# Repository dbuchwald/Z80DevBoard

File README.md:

# Z80DevBoard
Simple Z80 based prototyping and development board designed as extension to Arduino Mega 2560

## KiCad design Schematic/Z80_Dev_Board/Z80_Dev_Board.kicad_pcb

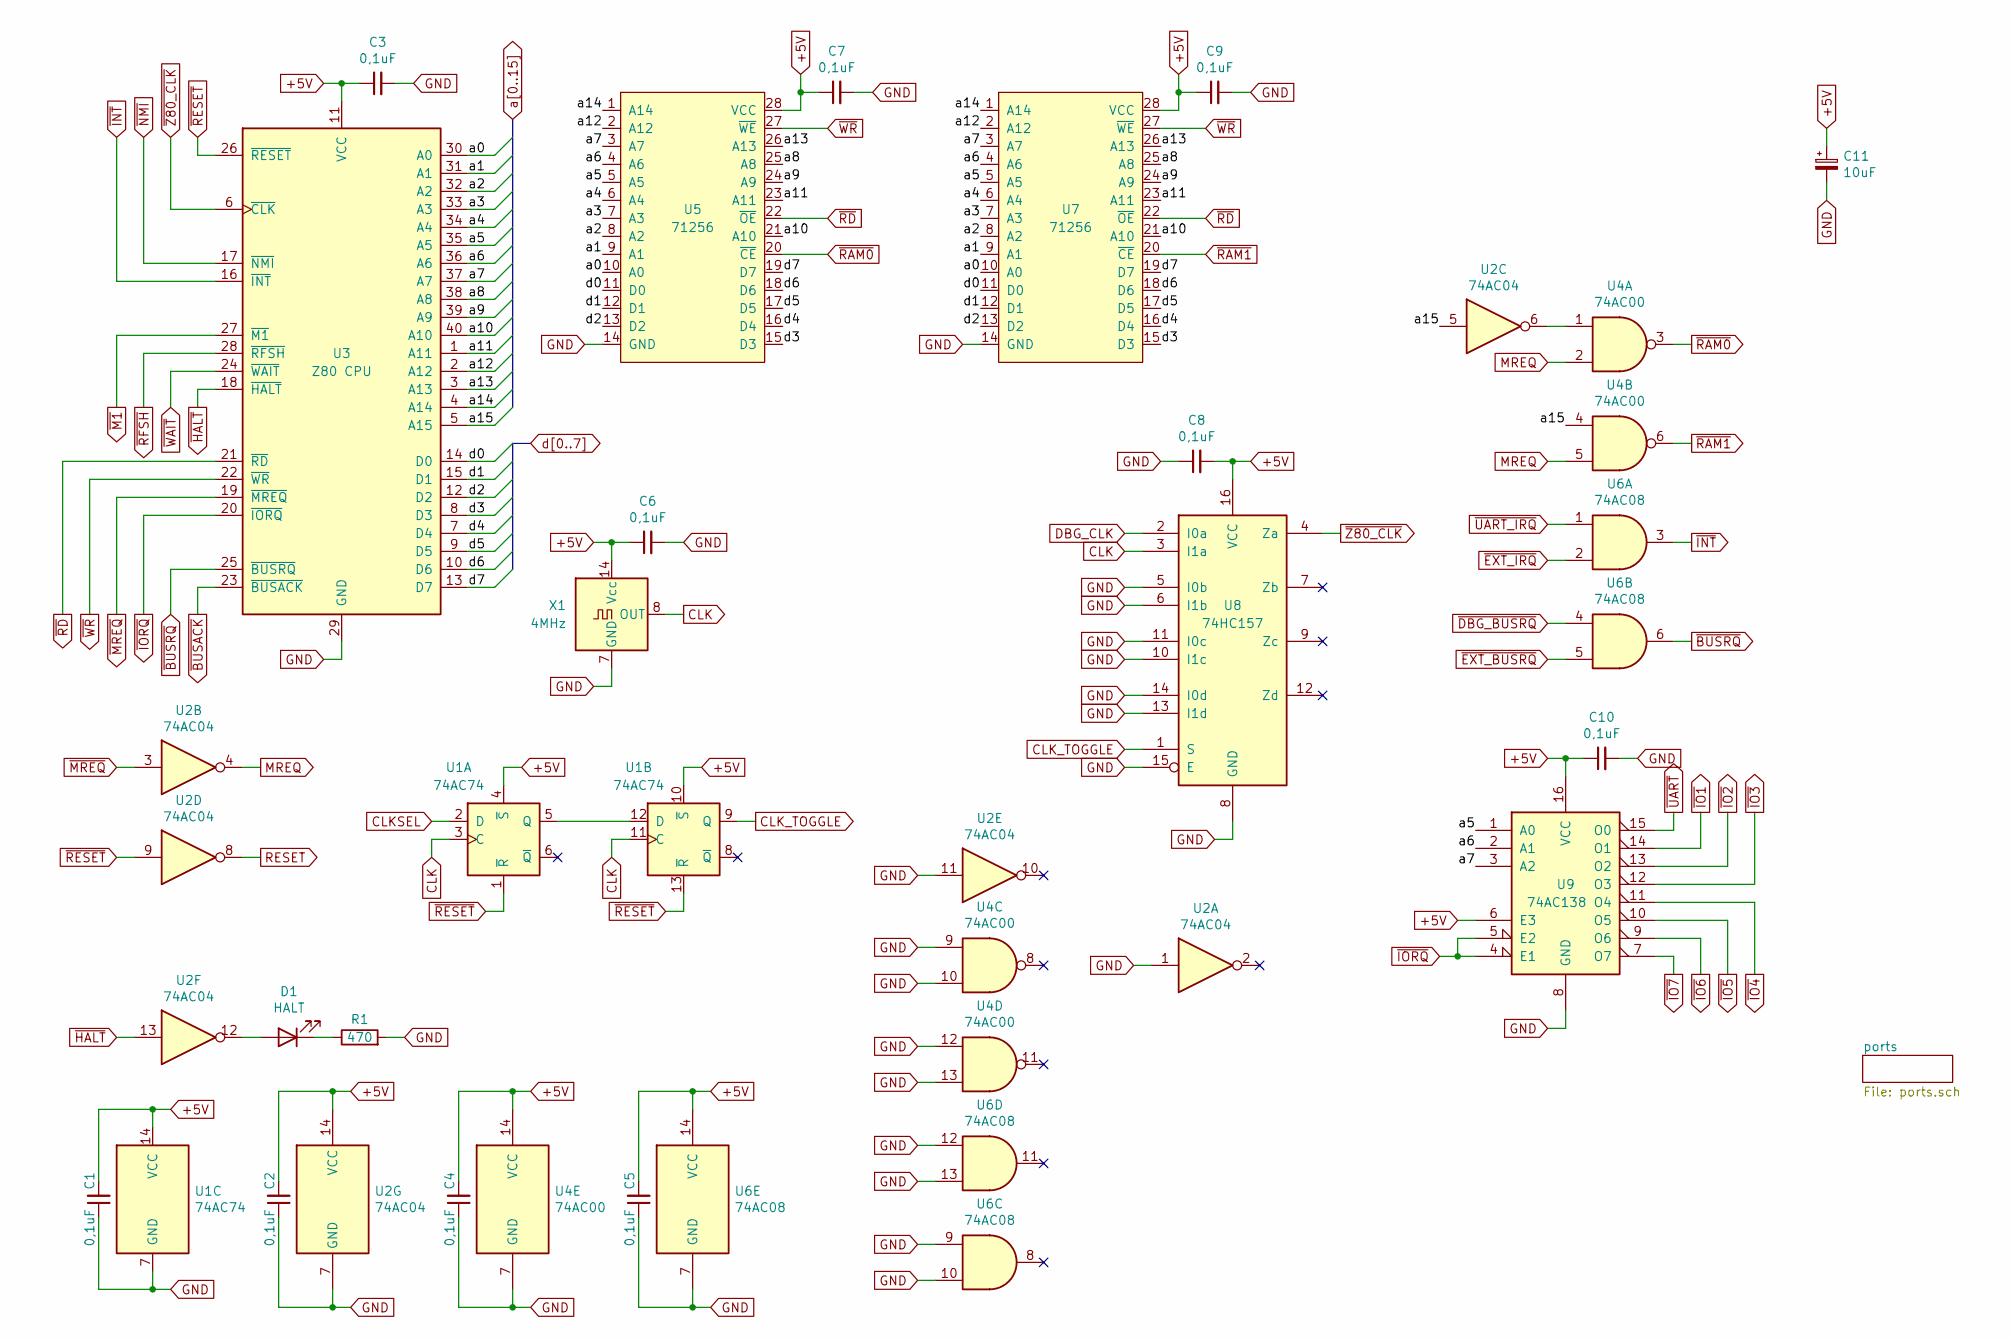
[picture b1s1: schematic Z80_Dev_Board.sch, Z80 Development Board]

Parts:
C1, C2, C3, C4, C5, C6, C7, C8, C9, C10: 0,1uF; C_1206_3216Metric_Pad1.42x1.75mm_HandSolder
C11: 10uF; CP_Radial_D4.0mm_P1.50mm
D1: HALT; LED_D3.0mm_Clear
R1: 470; R_1206_3216Metric_Pad1.30x1.75mm_HandSolder
U1: 74AC74; SOIC-14_3.9x8.7mm_P1.27mm
U2: 74AC04; SOIC-14_3.9x8.7mm_P1.27mm
U3: Z80 CPU; DIP-40_W15.24mm_Socket
U4: 74AC00; SOIC-14_3.9x8.7mm_P1.27mm
U5, U7: 71256; DIP-28_W7.62mm_Socket
U6: 74AC08; SOIC-14_3.9x8.7mm_P1.27mm
U8: 74HC157; SOIC-16_3.9x9.9mm_P1.27mm
U9: 74AC138; SOIC-16_3.9x9.9mm_P1.27mm
X1: 4MHz; Oscillator_DIP-14

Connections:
+5V: C1.2, C2.2, C3.1, C4.2, C5.2, C6.1, C7.1, C8.2, C9.1, C10.1, C11.1, U1.4 (~S), U1.10 (~S), U1.14 (VCC), U2.14 (VCC), U3.11 (VCC), U4.14 (VCC), U5.28 (VCC), U6.14 (VCC), U7.28 (VCC), U8.16 (VCC), U9.6 (E3), U9.16 (VCC), X1.14 (Vcc); also elsewhere on the board
CLK: U1.3 (C), U1.11 (C), U8.3 (I1a), X1.8 (OUT)
CLKSEL: U1.2 (D); also elsewhere on the board
CLK_TOGGLE: U1.9 (Q), U8.1 (S)
DBG_CLK: U8.2 (I0a); also elsewhere on the board
GND: C1.1, C2.1, C3.2, C4.1, C5.1, C6.2, C7.2, C8.1, C9.2, C10.2, C11.2, R1.2, U1.7 (GND), U2.1, U2.7 (GND), U2.11, U3.29 (GND), U4.7 (GND), U4.9, U4.10, U4.12, U4.13, U5.14 (GND), U6.7 (GND), U6.9, U6.10, U6.12, U6.13, U7.14 (GND), U8.5 (I0b), U8.6 (I1b), U8.8 (GND), U8.10 (I1c), U8.11 (I0c), U8.13 (I1d), U8.14 (I0d), U8.15 (E), U9.8 (GND), X1.7 (GND); also elsewhere on the board
MREQ: U2.4, U4.2, U4.5
unnamed: D1.1 (K), R1.1
unnamed: D1.2 (A), U2.12
unnamed: U1.5 (Q), U1.12 (D)
unnamed: U2.6, U4.1
RESET: U2.8; also elsewhere on the board
a0: U3.30 (A0), U5.10 (A0), U7.10 (A0); also elsewhere on the board
a1: U3.31 (A1), U5.9 (A1), U7.9 (A1); also elsewhere on the board
a2: U3.32 (A2), U5.8 (A2), U7.8 (A2); also elsewhere on the board
a3: U3.33 (A3), U5.7 (A3), U7.7 (A3); also elsewhere on the board
a4: U3.34 (A4), U5.6 (A4), U7.6 (A4); also elsewhere on the board
a5: U3.35 (A5), U5.5 (A5), U7.5 (A5), U9.1 (A0); also elsewhere on the board
a6: U3.36 (A6), U5.4 (A6), U7.4 (A6), U9.2 (A1); also elsewhere on the board
a7: U3.37 (A7), U5.3 (A7), U7.3 (A7), U9.3 (A2); also elsewhere on the board
a8: U3.38 (A8), U5.25 (A8), U7.25 (A8); also elsewhere on the board
a9: U3.39 (A9), U5.24 (A9), U7.24 (A9); also elsewhere on the board
a10: U3.40 (A10), U5.21 (A10), U7.21 (A10); also elsewhere on the board
a11: U3.1 (A11), U5.23 (A11), U7.23 (A11); also elsewhere on the board
a12: U3.2 (A12), U5.2 (A12), U7.2 (A12); also elsewhere on the board
a13: U3.3 (A13), U5.26 (A13), U7.26 (A13); also elsewhere on the board
a14: U3.4 (A14), U5.1 (A14), U7.1 (A14); also elsewhere on the board
a15: U2.5, U3.5 (A15), U4.4; also elsewhere on the board
d0: U3.14 (D0), U5.11 (D0), U7.11 (D0); also elsewhere on the board
d1: U3.15 (D1), U5.12 (D1), U7.12 (D1); also elsewhere on the board
d2: U3.12 (D2), U5.13 (D2), U7.13 (D2); also elsewhere on the board
d3: U3.8 (D3), U5.15 (D3), U7.15 (D3); also elsewhere on the board
d4: U3.7 (D4), U5.16 (D4), U7.16 (D4); also elsewhere on the board
d5: U3.9 (D5), U5.17 (D5), U7.17 (D5); also elsewhere on the board
d6: U3.10 (D6), U5.18 (D6), U7.18 (D6); also elsewhere on the board
d7: U3.13 (D7), U5.19 (D7), U7.19 (D7); also elsewhere on the board
~BUSACK: U3.23 (~BUSACK~); also elsewhere on the board
~BUSRQ: U3.25 (~BUSRQ~), U6.6
~DBG_BUSRQ: U6.4; also elsewhere on the board
~EXT_BUSRQ: U6.5; also elsewhere on the board
~EXT_IRQ: U6.2; also elsewhere on the board
~HALT: U2.13, U3.18 (~HALT~); also elsewhere on the board
~INT: U3.16 (~INT~), U6.3
~IO1: U9.14 (O1); also elsewhere on the board
~IO2: U9.13 (O2); also elsewhere on the board
~IO3: U9.12 (O3); also elsewhere on the board
~IO4: U9.11 (O4); also elsewhere on the board
~IO5: U9.10 (O5); also elsewhere on the board
~IO6: U9.9 (O6); also elsewhere on the board
~IO7: U9.7 (O7); also elsewhere on the board
~IORQ: U3.20 (~IORQ~), U9.4 (E1), U9.5 (E2); also elsewhere on the board
~M1: U3.27 (~M1~); also elsewhere on the board
~MREQ: U2.3, U3.19 (~MREQ~); also elsewhere on the board
~NMI: U3.17 (~NMI~); also elsewhere on the board
~RAM0: U4.3, U5.20 (~CE)
~RAM1: U4.6, U7.20 (~CE)
~RD: U3.21 (~RD~), U5.22 (~OE), U7.22 (~OE); also elsewhere on the board
~RESET: U1.1 (~R), U1.13 (~R), U2.9, U3.26 (~RESET~); also elsewhere on the board
~RFSH: U3.28 (~RFSH~); also elsewhere on the board
~UART: U9.15 (O0); also elsewhere on the board
~UART_IRQ: U6.1; also elsewhere on the board
~WAIT: U3.24 (~WAIT~); also elsewhere on the board
~WR: U3.22 (~WR~), U5.27 (~WE), U7.27 (~WE); also elsewhere on the board
~Z80_CLK: U3.6 (~CLK~), U8.4 (Za); also elsewhere on the board

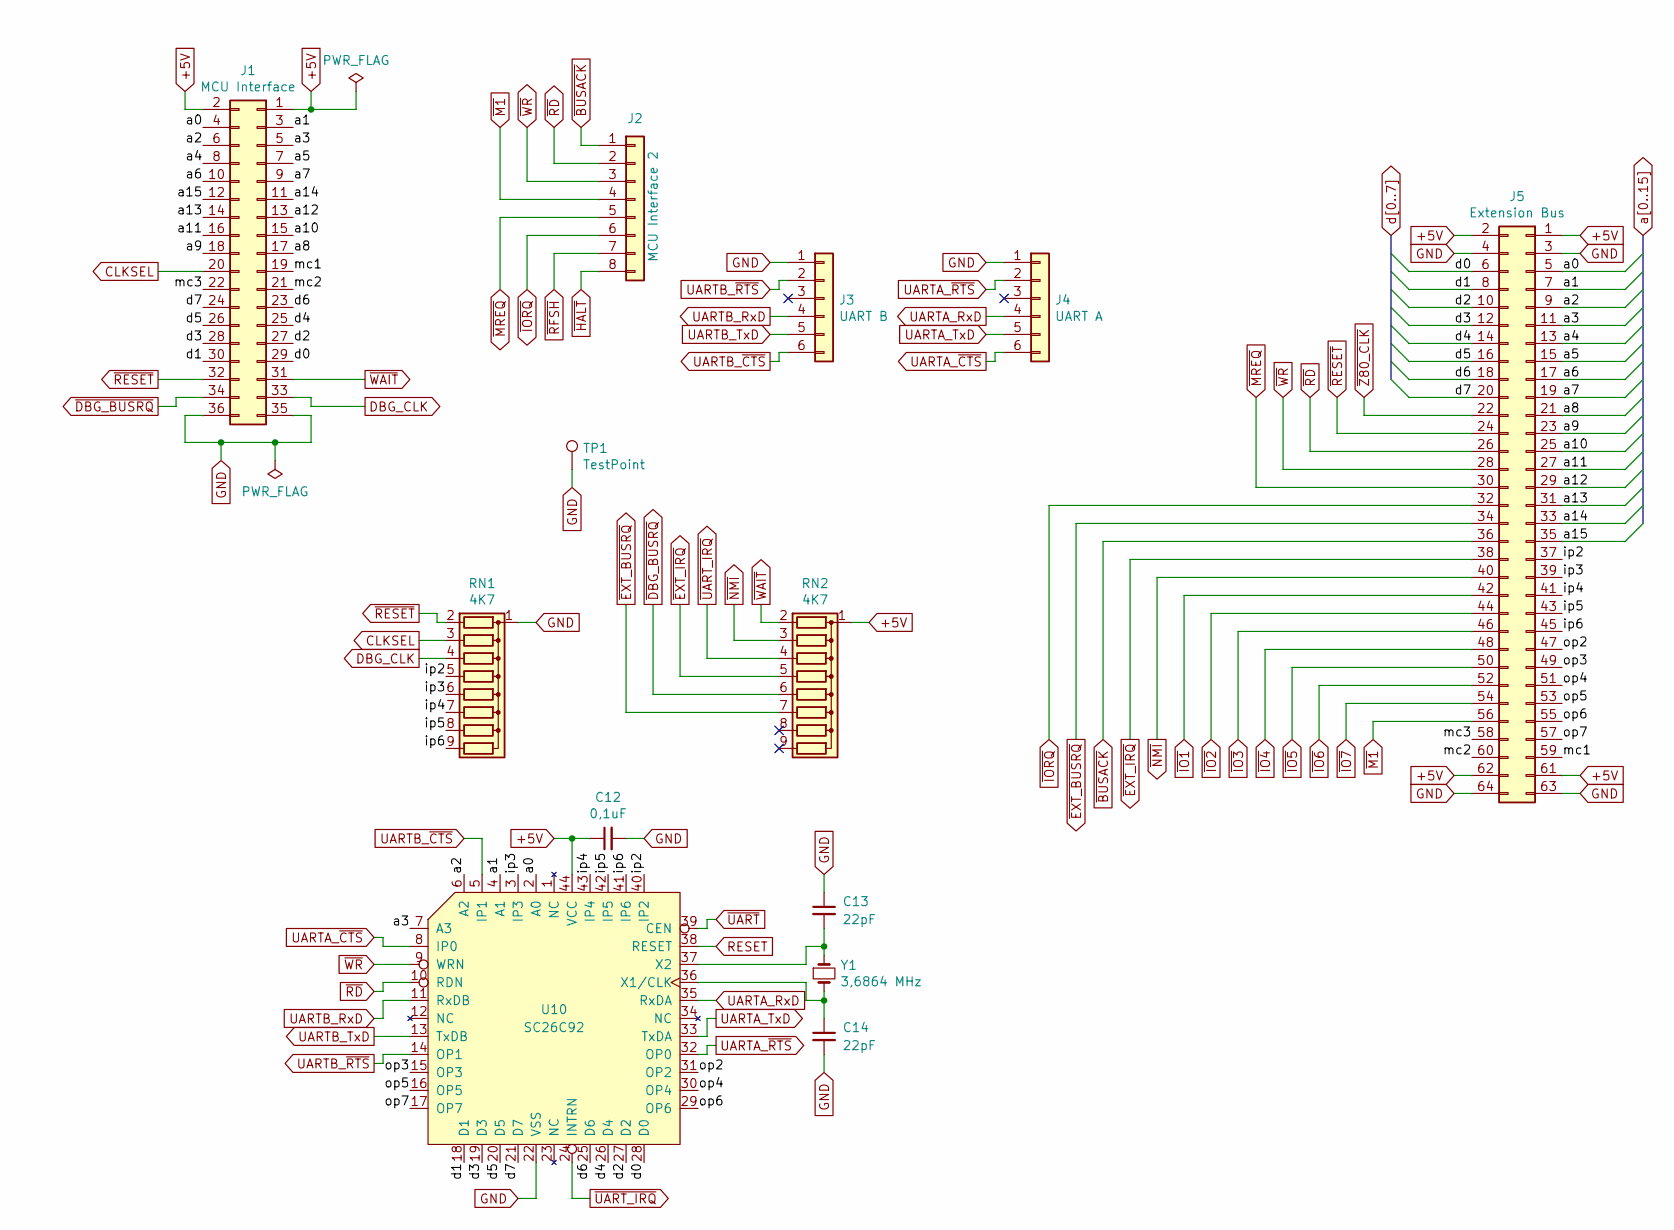
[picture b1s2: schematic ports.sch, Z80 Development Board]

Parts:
C12: 0,1uF; C_1206_3216Metric_Pad1.42x1.75mm_HandSolder
C13, C14: 22pF; C_1206_3216Metric_Pad1.33x1.80mm_HandSolder
J1: MCU Interface; PinHeader_2x18_P2.54mm_Vertical
J2: MCU Interface 2; PinSocket_1x08_P2.54mm_Vertical
J3: UART B; PinHeader_1x06_P2.54mm_Horizontal
J4: UART A; PinHeader_1x06_P2.54mm_Horizontal
J5: Extension Bus; PinSocket_2x32_P2.54mm_Vertical
RN1, RN2: 4K7; R_Array_SIP9
TP1: TestPoint; TestPoint_Keystone_5005-5009_Compact
U10: SC26C92; PLCC-44_THT-Socket
Y1: 3,6864 MHz; Crystal_HC49-U_Vertical

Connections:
+5V: C12.1, J1.1, J1.2, J5.1, J5.2, J5.61, J5.62, RN2.1 (common), U10.44 (VCC); also elsewhere on the board
/ports/ip2: J5.37, RN1.5 (R4), U10.40 (IP2)
/ports/ip3: J5.39, RN1.6 (R5), U10.3 (IP3)
/ports/ip4: J5.41, RN1.7 (R6), U10.43 (IP4)
/ports/ip5: J5.43, RN1.8 (R7), U10.42 (IP5)
/ports/ip6: J5.45, RN1.9 (R8), U10.41 (IP6)
/ports/mc1: J1.19, J5.59
/ports/mc2: J1.21, J5.60
/ports/mc3: J1.22, J5.58
/ports/op2: J5.47, U10.31 (OP2)
/ports/op3: J5.49, U10.15 (OP3)
/ports/op4: J5.51, U10.30 (OP4)
/ports/op5: J5.53, U10.16 (OP5)
/ports/op6: J5.55, U10.29 (OP6)
/ports/op7: J5.57, U10.17 (OP7)
CLKSEL: J1.20, RN1.3 (R2); also elsewhere on the board
DBG_CLK: J1.33, RN1.4 (R3); also elsewhere on the board
GND: C12.2, C13.1, C14.2, J1.35, J1.36, J3.1, J4.1, J5.3, J5.4, J5.63, J5.64, RN1.1 (common), TP1.1, U10.22 (VSS); also elsewhere on the board
unnamed: C13.2, U10.37 (X2), Y1.1
unnamed: C14.1, U10.36 (X1/CLK), Y1.2
RESET: U10.38 (RESET); also elsewhere on the board
UARTA_RxD: J4.4, U10.35 (RxDA)
UARTA_TxD: J4.5, U10.33 (TxDA)
UARTA_~CTS: J4.6, U10.8 (IP0)
UARTA_~RTS: J4.2, U10.32 (OP0)
UARTB_RxD: J3.4, U10.11 (RxDB)
UARTB_TxD: J3.5, U10.13 (TxDB)
UARTB_~CTS: J3.6, U10.5 (IP1)
UARTB_~RTS: J3.2, U10.14 (OP1)
a0: J1.4, J5.5, U10.2 (A0); also elsewhere on the board
a1: J1.3, J5.7, U10.4 (A1); also elsewhere on the board
a2: J1.6, J5.9, U10.6 (A2); also elsewhere on the board
a3: J1.5, J5.11, U10.7 (A3); also elsewhere on the board
a4: J1.8, J5.13; also elsewhere on the board
a5: J1.7, J5.15; also elsewhere on the board
a6: J1.10, J5.17; also elsewhere on the board
a7: J1.9, J5.19; also elsewhere on the board
a8: J1.17, J5.21; also elsewhere on the board
a9: J1.18, J5.23; also elsewhere on the board
a10: J1.15, J5.25; also elsewhere on the board
a11: J1.16, J5.27; also elsewhere on the board
a12: J1.13, J5.29; also elsewhere on the board
a13: J1.14, J5.31; also elsewhere on the board
a14: J1.11, J5.33; also elsewhere on the board
a15: J1.12, J5.35; also elsewhere on the board
d0: J1.29, J5.6, U10.28 (D0); also elsewhere on the board
d1: J1.30, J5.8, U10.18 (D1); also elsewhere on the board
d2: J1.27, J5.10, U10.27 (D2); also elsewhere on the board
d3: J1.28, J5.12, U10.19 (D3); also elsewhere on the board
d4: J1.25, J5.14, U10.26 (D4); also elsewhere on the board
d5: J1.26, J5.16, U10.20 (D5); also elsewhere on the board
d6: J1.23, J5.18, U10.25 (D6); also elsewhere on the board
d7: J1.24, J5.20, U10.21 (D7); also elsewhere on the board
~BUSACK: J2.1, J5.36; also elsewhere on the board
~DBG_BUSRQ: J1.34, RN2.6 (R5); also elsewhere on the board
~EXT_BUSRQ: J5.34, RN2.7 (R6); also elsewhere on the board
~EXT_IRQ: J5.38, RN2.5 (R4); also elsewhere on the board
~HALT: J2.8; also elsewhere on the board
~IO1: J5.42; also elsewhere on the board
~IO2: J5.44; also elsewhere on the board
~IO3: J5.46; also elsewhere on the board
~IO4: J5.48; also elsewhere on the board
~IO5: J5.50; also elsewhere on the board
~IO6: J5.52; also elsewhere on the board
~IO7: J5.54; also elsewhere on the board
~IORQ: J2.6, J5.32; also elsewhere on the board
~M1: J2.4, J5.56; also elsewhere on the board
~MREQ: J2.5, J5.30; also elsewhere on the board
~NMI: J5.40, RN2.3 (R2); also elsewhere on the board
~RD: J2.2, J5.26, U10.10 (RDN); also elsewhere on the board
~RESET: J1.32, J5.24, RN1.2 (R1); also elsewhere on the board
~RFSH: J2.7; also elsewhere on the board
~UART: U10.39 (CEN); also elsewhere on the board
~UART_IRQ: RN2.4 (R3), U10.24 (INTRN); also elsewhere on the board
~WAIT: J1.31, RN2.2 (R1); also elsewhere on the board
~WR: J2.3, J5.28, U10.9 (WRN); also elsewhere on the board
~Z80_CLK: J5.22; also elsewhere on the board

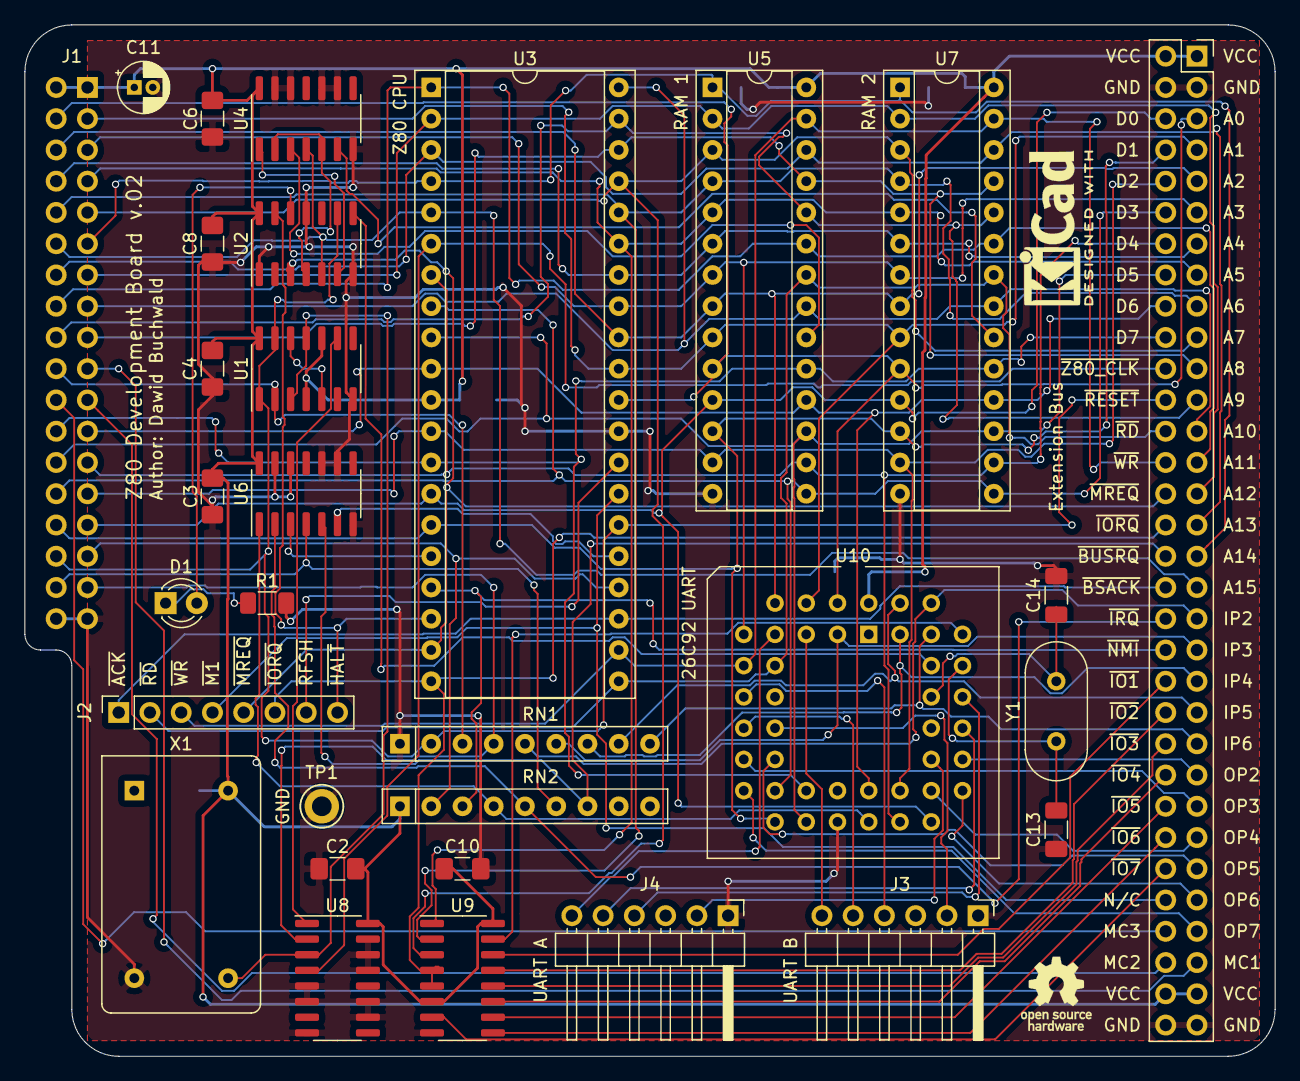
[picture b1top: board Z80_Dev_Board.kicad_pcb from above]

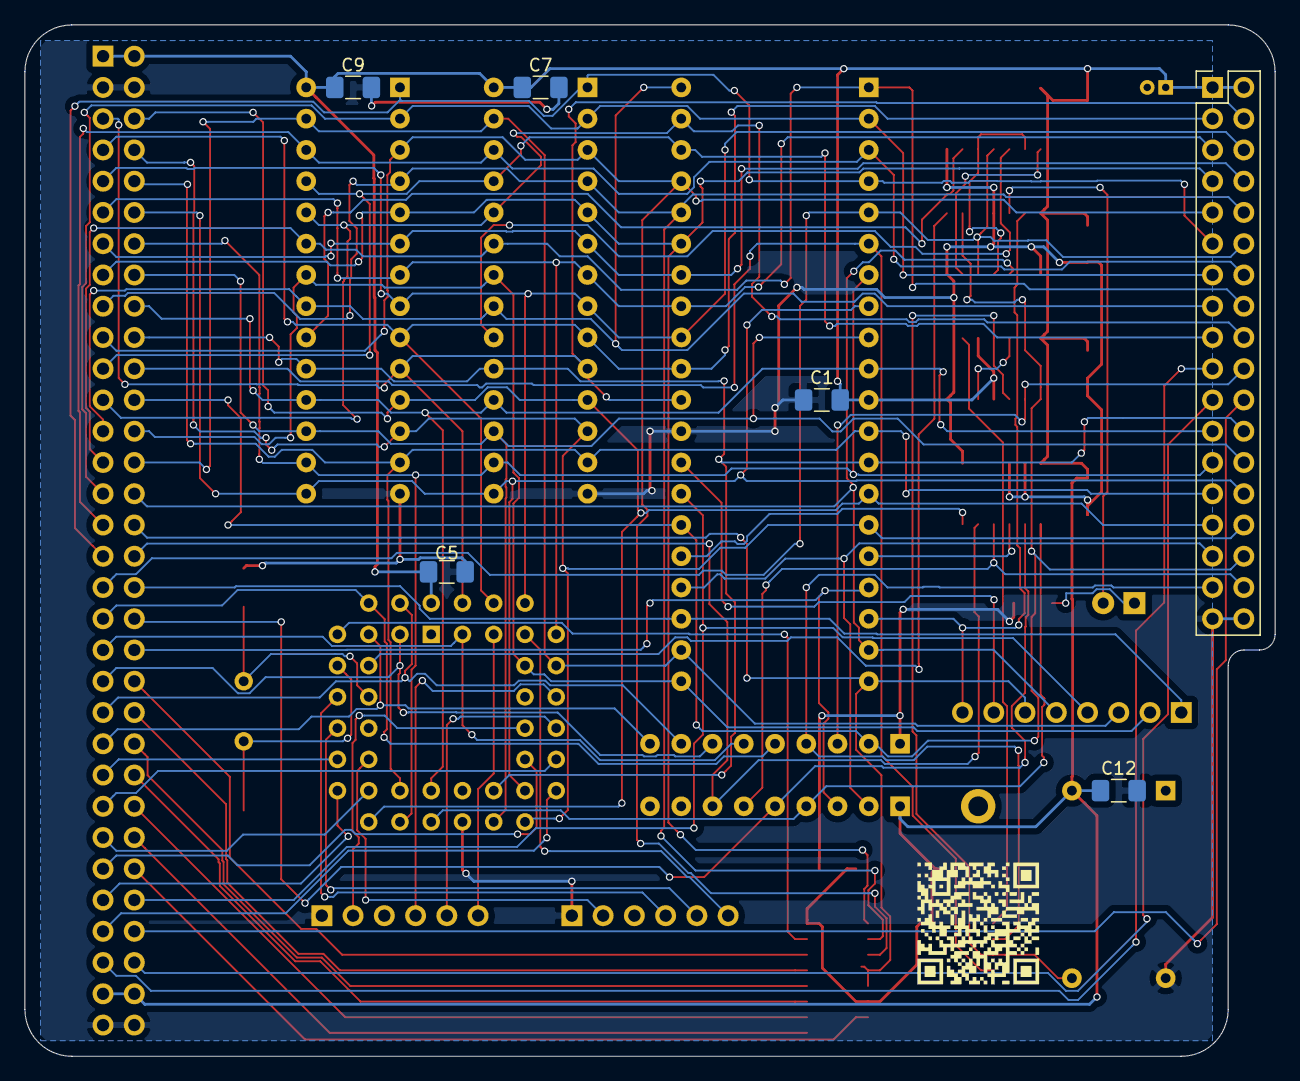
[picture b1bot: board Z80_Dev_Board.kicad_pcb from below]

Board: 2 copper layers, 101.6 x 83.8 mm, 37 parts (7 on the bottom side), 88 nets.

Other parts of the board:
QR*****: z80_github

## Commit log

2020-11-15 Initial repo creation
2020-11-15 Initial schematic commit - CPU, RAM, MCU Interface
2020-11-15 Added basic glue logic and clock toggle circuit
2020-11-15 Completed basic schematic
2020-11-15 Update to project file
2020-11-17 Updated schematic
2020-11-17 Added HALT LED, moved things around
2020-11-17 Started second PCB attempt
2020-11-17 Added global bus labels
2020-11-17 PCB designed
2020-11-17 PCB RC1
2020-11-19 Small cosmetic updates to PCB
2020-11-19 Completed PCB rework
2020-11-19 PCB RC2 with gerbers
2020-11-19 PCB RC3 with gerbers
2020-11-19 Initial adaptation of DB6502 supervisor to Z80 board
2020-11-25 First working version of the supervisor
2020-11-25 First ROM created and tested, basic build process defined
2020-11-28 First UART test program
2021-01-30 Started working on updated PCB with IO decoder
2021-01-30 Replaced A15 by A07 in UART selection
2021-03-18 New version of the board created
2021-03-19 Added super-fast mode
2021-03-20 Started working on IRQ UART program
2021-03-20 Implemented basic UART IRQ based RX-TX loop
2021-03-20 Small update to silkscreen
2021-04-25 Updated gerbers for second revision of the board
2021-05-08 Replaced THT caps/resistors with SMD
2021-05-08 Removed CSV file
2021-05-10 Last-minute updates to board layout (and clock toggle schematic)
2021-05-11 Added QR code for github project
2021-05-18 Added support for external oscillator and new board
2021-05-20 Adapted code to board version 2 (proper I/O decoding)
